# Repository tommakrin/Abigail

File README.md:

The code here is mainly Hasu's project for a custom keyboard, a bit modified. CAD files for the PCB and case are mine.
=======
# Abigail
Abigail is a project that started in February 2015. It's purpose is the construction of a mechanical keyboard from scratch, including the PCB design, case construction, microcontroller and firmware installation.

The code here is mainly Hasu's project for a custom keyboard, a bit modified. CAD files for the PCB and case are mine.

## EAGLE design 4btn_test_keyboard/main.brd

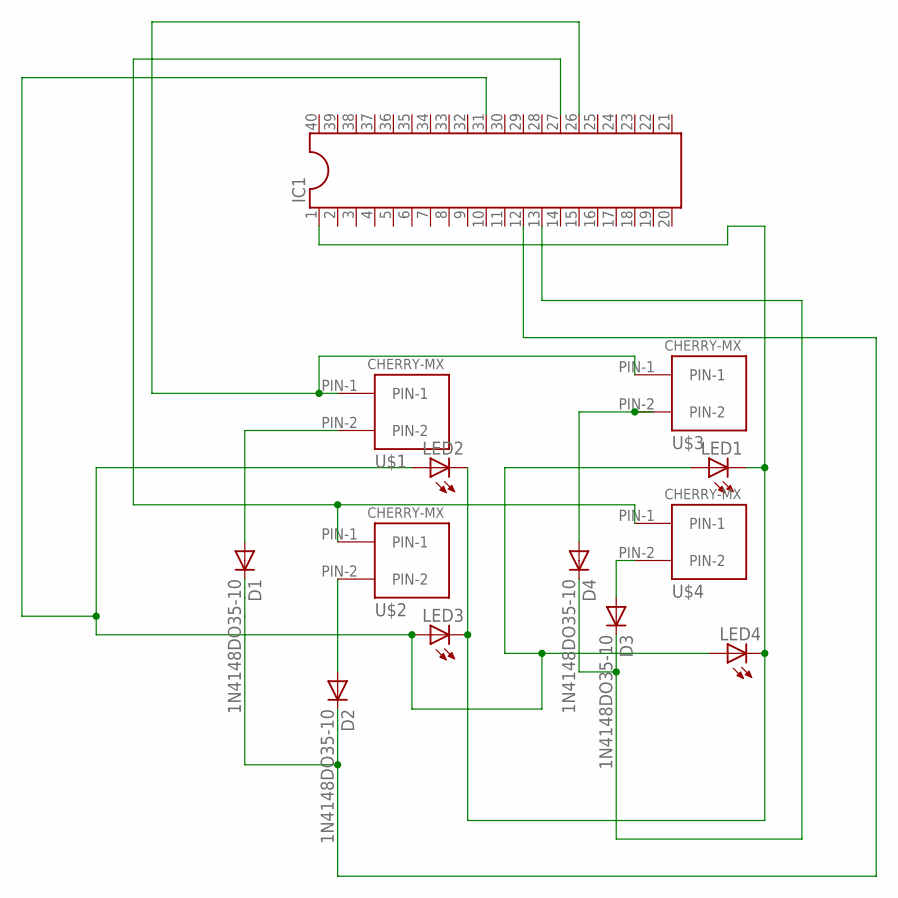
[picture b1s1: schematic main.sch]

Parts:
D1, D2, D3, D4: 1N4148DO35-10; DO35-10
IC1: DIL40
LED1, LED2, LED3, LED4: LED3MM
U$1, U$2, U$3, U$4: CHERRY-MX-I

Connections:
unnamed: D1.A, U$1.PIN-2
unnamed: D2.A, U$2.PIN-2
unnamed: D4.A, U$3.PIN-2
unnamed: D3.A, U$4.PIN-2
unnamed: D3.C, D4.C, IC1.13
unnamed: IC1.27, U$2.PIN-1, U$4.PIN-1
unnamed: IC1.26, U$1.PIN-1, U$3.PIN-1
unnamed: D1.C, D2.C, IC1.12
unnamed: IC1.1, LED1.K (C), LED2.K (C), LED3.K (C), LED4.K (C)
unnamed: IC1.31, LED1.A, LED2.A, LED3.A, LED4.A

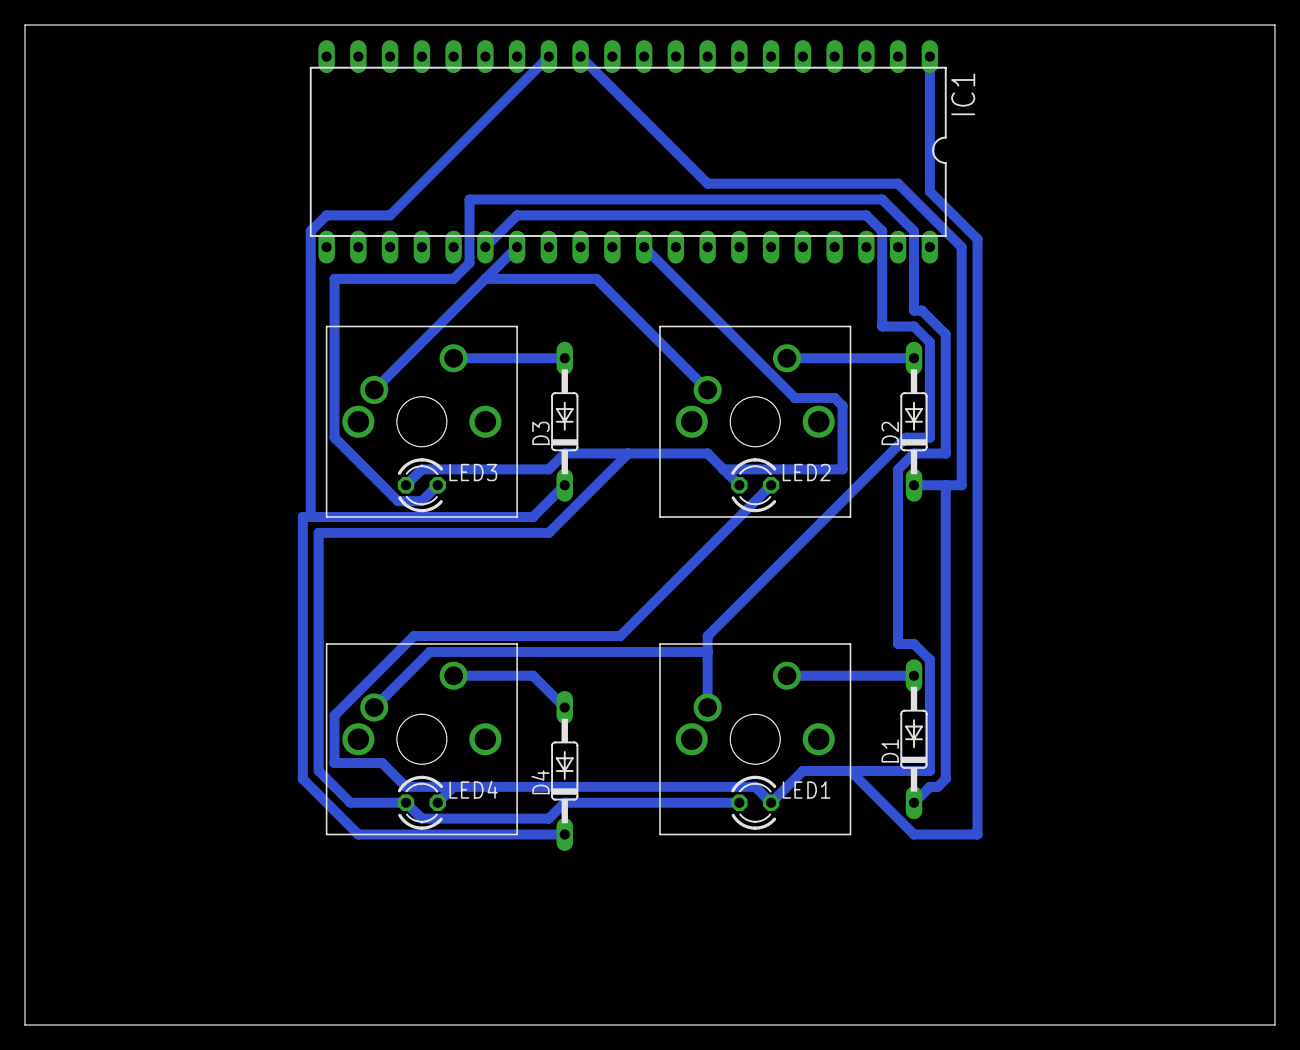
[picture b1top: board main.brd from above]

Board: 2 copper layers, 100.0 x 80.0 mm, 13 parts (0 on the bottom side), 10 nets.

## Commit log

2016-05-09 Update commit
2016-05-09 Update repo
